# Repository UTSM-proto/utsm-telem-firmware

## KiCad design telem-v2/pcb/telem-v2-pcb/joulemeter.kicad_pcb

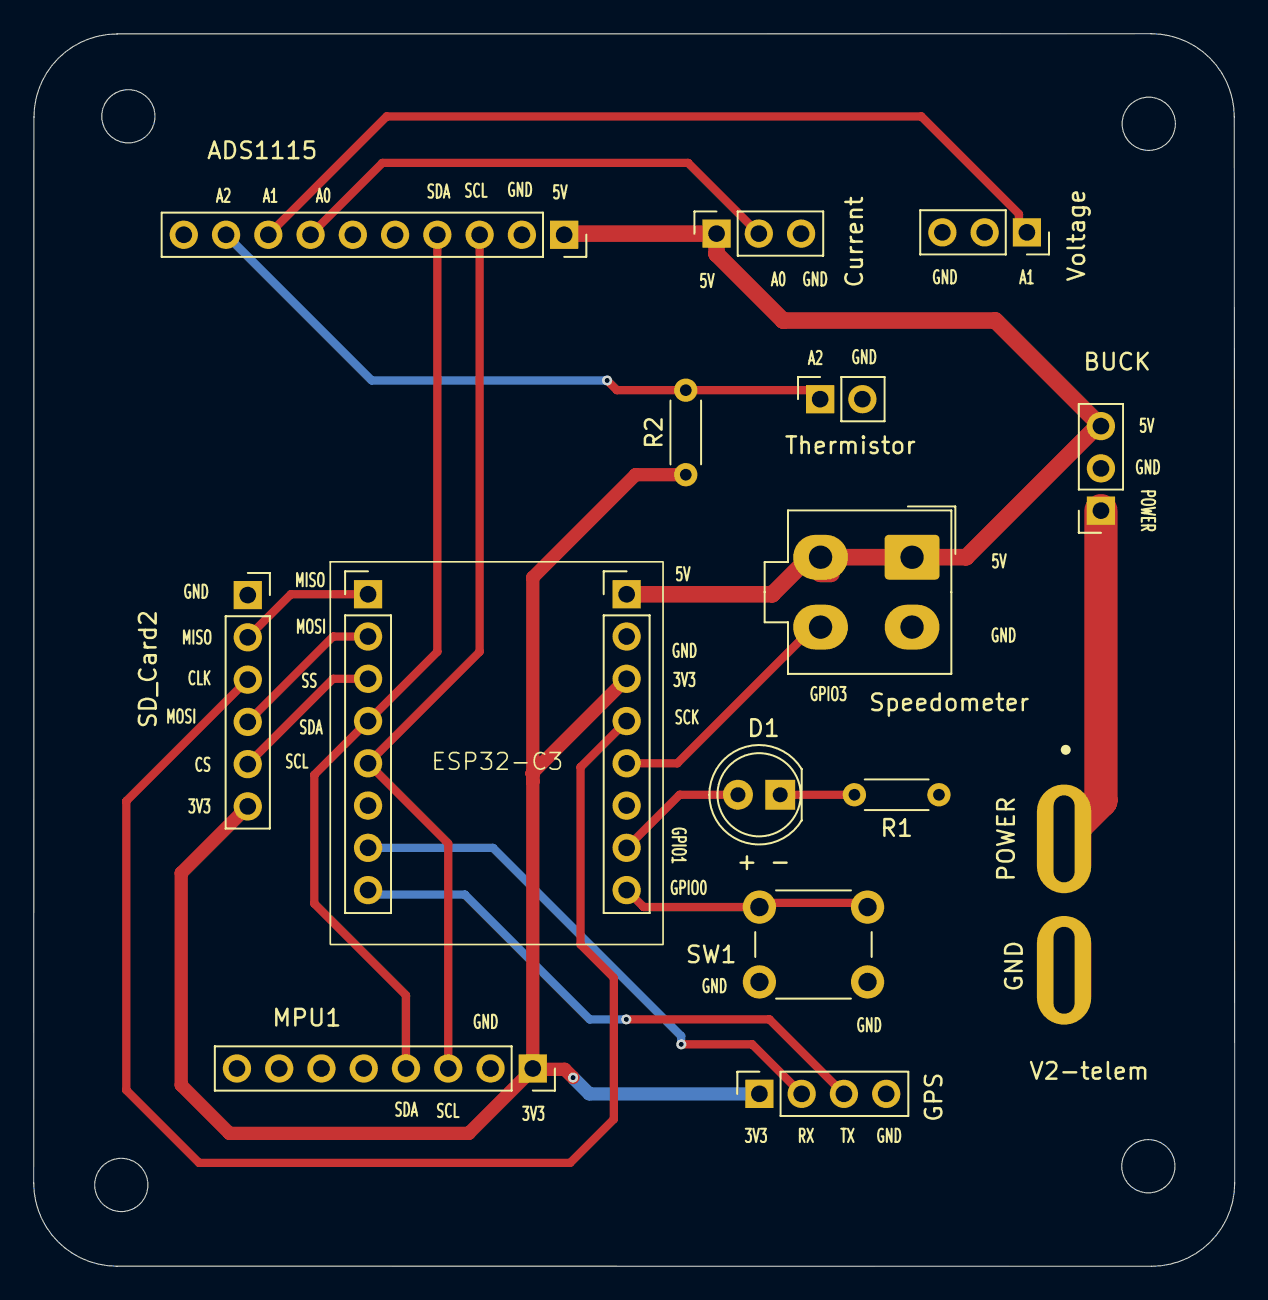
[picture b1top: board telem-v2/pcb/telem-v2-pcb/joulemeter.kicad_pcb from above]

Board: 2 copper layers, 72.2 x 74.1 mm, 15 parts (0 on the bottom side), 19 nets.

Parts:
ADS1115: Conn_01x10_Pin; PinSocket_1x10_P2.54mm_Vertical
BuckConverter1: Conn_01x03_Pin; PinSocket_1x03_P2.54mm_Vertical
Current: Conn_01x03_Pin; PinSocket_1x03_P2.54mm_Vertical
D1: LED; LED_D5.0mm
ESP32-C3: C3; ESP32C3
GPS: Conn_01x04_Pin; PinSocket_1x04_P2.54mm_Vertical
J1: ASMPR45-1X2-RK; APP_ASMPR45-1X2-RK
J2: Speedometer; Molex_Mini-Fit_Jr_5566-04A_2x02_P4.20mm_Vertical
MPU1: Conn_01x8_Pin; PinSocket_1x08_P2.54mm_Vertical
R1: R; R_Axial_DIN0204_L3.6mm_D1.6mm_P5.08mm_Horizontal
R2: 33k; R_Axial_DIN0204_L3.6mm_D1.6mm_P5.08mm_Horizontal
SD_Card2: Conn_01x6_Pin; PinSocket_1x06_P2.54mm_Vertical
SW1: SW_Push; SW_PUSH_6mm_H5mm
TH1: Thermistor; PinSocket_1x02_P2.54mm_Vertical
Voltage: Conn_01x03_Pin; PinSocket_1x03_P2.54mm_Vertical

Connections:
3.3V: ESP32-C3.13 (3.3V), GPS.1 (VCC), MPU1.1 (VCC), R2.1, SD_Card2.6 (3.3V)
+5V: ADS1115.1 (VDD), BuckConverter1.3 (VCC), Current.1 (VCC), ESP32-C3.11 (5V), J2.1, J2.3
External_Power: BuckConverter1.1 (External_Power), J1.1
GND: ADS1115.2 (GND), BuckConverter1.2 (GND), Current.3 (GND), ESP32-C3.12 (GND), GPS.4 (GND), J1.2, J2.2, MPU1.2 (GND), R1.2, SD_Card2.1 (GND), SW1.2, TH1.2, Voltage.3 (-)
MISO: ESP32-C3.5 (5-MISO), SD_Card2.2 (MISO)
MOSI: ESP32-C3.6 (6-MOSI), SD_Card2.4 (MOSI)
unnamed: ADS1115.7 (A0), Current.2 (OUT)
unnamed: ADS1115.8 (A1), Voltage.1 (S)
unnamed: ADS1115.9 (A2), R2.2, TH1.1
unnamed: D1.2 (A), ESP32-C3.1 (GPIO1)
unnamed: D1.1 (K), R1.1
unnamed: ESP32-C3.7 (7-SS), SD_Card2.5 (CS)
unnamed: ESP32-C3.0 (GPIO0), SW1.1
unnamed: ESP32-C3.3 (GPIO3), J2.4
RX: ESP32-C3.20 (20-RX), GPS.2 (RX)
SCK: ESP32-C3.4 (GPIO4-SCK), SD_Card2.3 (CLK)
SCL: ADS1115.3 (SCL), ESP32-C3.9 (9-SCL), MPU1.3 (SCL)
SDA: ADS1115.4 (SDA), ESP32-C3.8 (8-SDA), MPU1.4 (SDA)
TX: ESP32-C3.21 (21-TX), GPS.3 (TX)

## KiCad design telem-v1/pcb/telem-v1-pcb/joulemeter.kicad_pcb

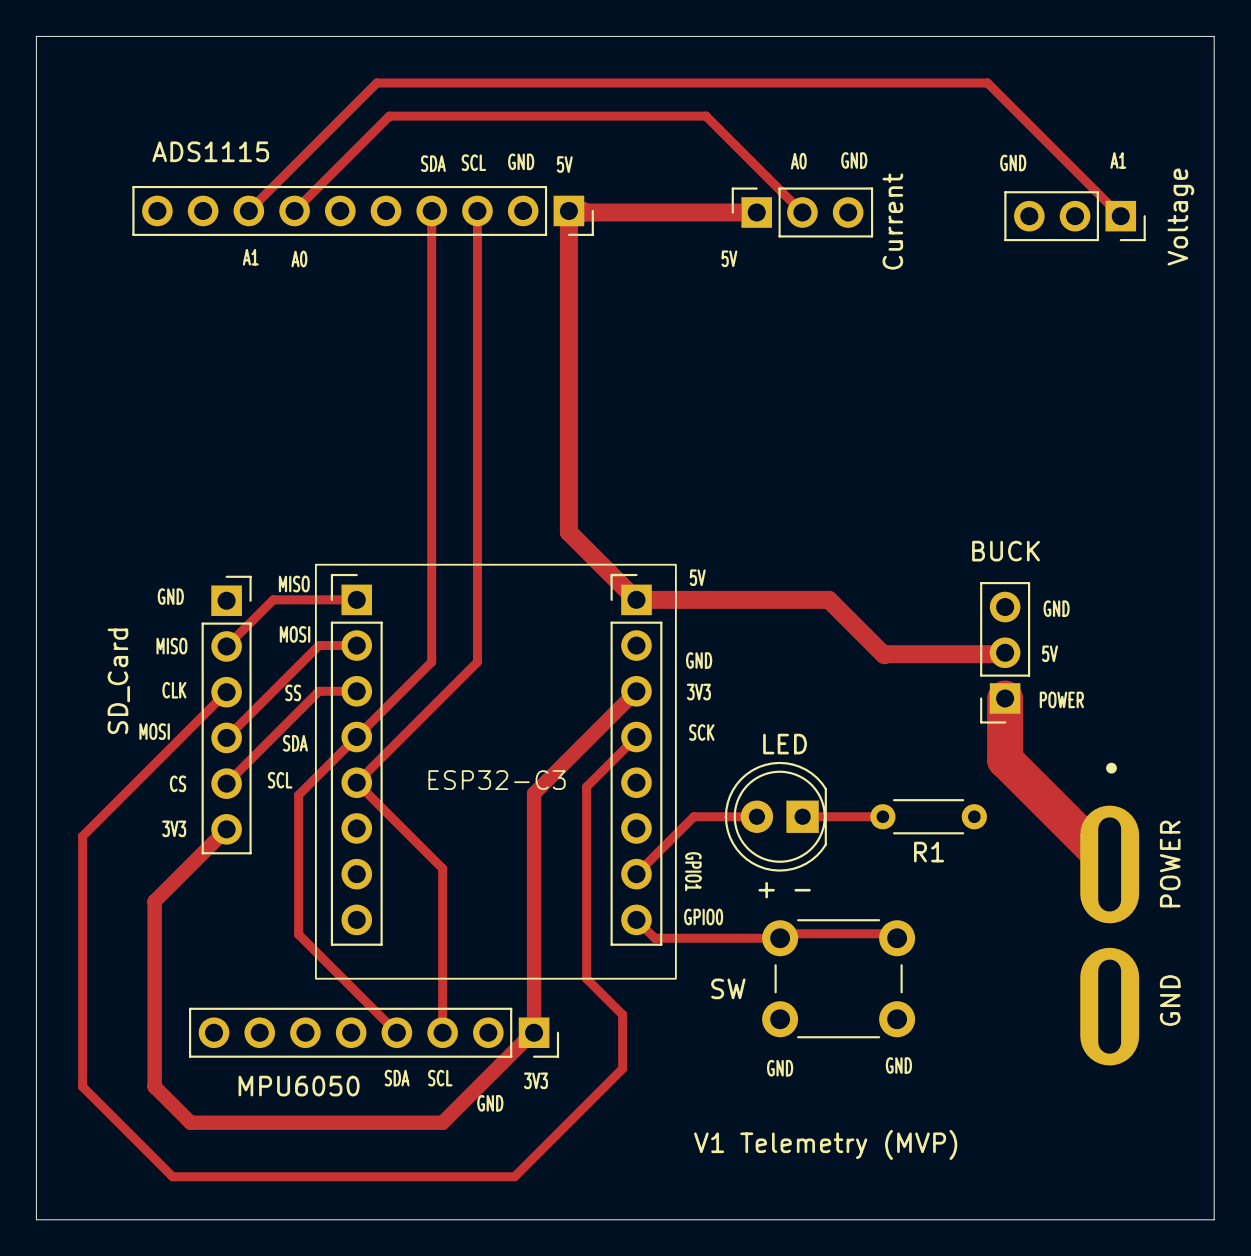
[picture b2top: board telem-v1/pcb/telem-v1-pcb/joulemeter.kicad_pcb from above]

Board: 2 copper layers, 65.4 x 65.7 mm, 11 parts (0 on the bottom side), 15 nets.

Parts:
ADS1115: Conn_01x10_Pin; PinSocket_1x10_P2.54mm_Vertical
BuckConverter: Conn_01x03_Pin; PinSocket_1x03_P2.54mm_Vertical
Current: Conn_01x03_Pin; PinSocket_1x03_P2.54mm_Vertical
ESP32-C3: C3; ESP32C3
J1: ASMPR45-1X2-RK; APP_ASMPR45-1X2-RK
LED: LED; LED_D5.0mm
MPU6050: Conn_01x8_Pin; PinSocket_1x08_P2.54mm_Vertical
R1: R; R_Axial_DIN0204_L3.6mm_D1.6mm_P5.08mm_Horizontal
SD_Card: Conn_01x6_Pin; PinSocket_1x06_P2.54mm_Vertical
SW: SW_Push; SW_PUSH_6mm_H5mm
Voltage: Conn_01x03_Pin; PinSocket_1x03_P2.54mm_Vertical

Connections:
3.3V: ESP32-C3.13 (3.3V), MPU6050.1 (VCC), SD_Card.6 (3.3V)
+5V: ADS1115.1 (VDD), BuckConverter.2 (VCC), Current.1 (VCC), ESP32-C3.11 (5V)
External_Power: BuckConverter.1 (External_Power), J1.1
GND: ADS1115.2 (GND), BuckConverter.3 (GND), Current.3 (GND), ESP32-C3.12 (GND), J1.2, MPU6050.2 (GND), R1.2, SD_Card.1 (GND), SW.2, Voltage.3 (-)
MISO: ESP32-C3.5 (5-MISO), SD_Card.2 (MISO)
MOSI: ESP32-C3.6 (6-MOSI), SD_Card.4 (MOSI)
unnamed: ADS1115.7 (A0), Current.2 (OUT)
unnamed: ADS1115.8 (A1), Voltage.1 (S)
unnamed: ESP32-C3.1 (GPIO1), LED.2 (A)
unnamed: LED.1 (K), R1.1
unnamed: ESP32-C3.7 (7-SS), SD_Card.5 (CS)
unnamed: ESP32-C3.0 (GPIO0), SW.1
SCK: ESP32-C3.4 (GPIO4-SCK), SD_Card.3 (CLK)
SCL: ADS1115.3 (SCL), ESP32-C3.9 (9-SCL), MPU6050.3 (SCL)
SDA: ADS1115.4 (SDA), ESP32-C3.8 (8-SDA), MPU6050.4 (SDA)

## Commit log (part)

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2026-06-13 Rename firmware sketch for clarity
2026-06-18 Added GPS to v1 telemetry schematic with connections and footprints, but not on pcb
2026-06-24 new gps code
2026-06-25 Initial Thermistor code using the ADS1115 to measure temperature
2026-06-25 this does not work yet. it is in progress
